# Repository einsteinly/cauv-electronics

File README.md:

**This repository has been moved to https://github.com/CambridgeAUV/cauv_electronics and is no longer maintained**

# cauv-electronics

This is the electronics repository for our newest vehicle. This library is dependent on the Adam Greig KiCAD library. Additional components are added in the cauv_lib directory.

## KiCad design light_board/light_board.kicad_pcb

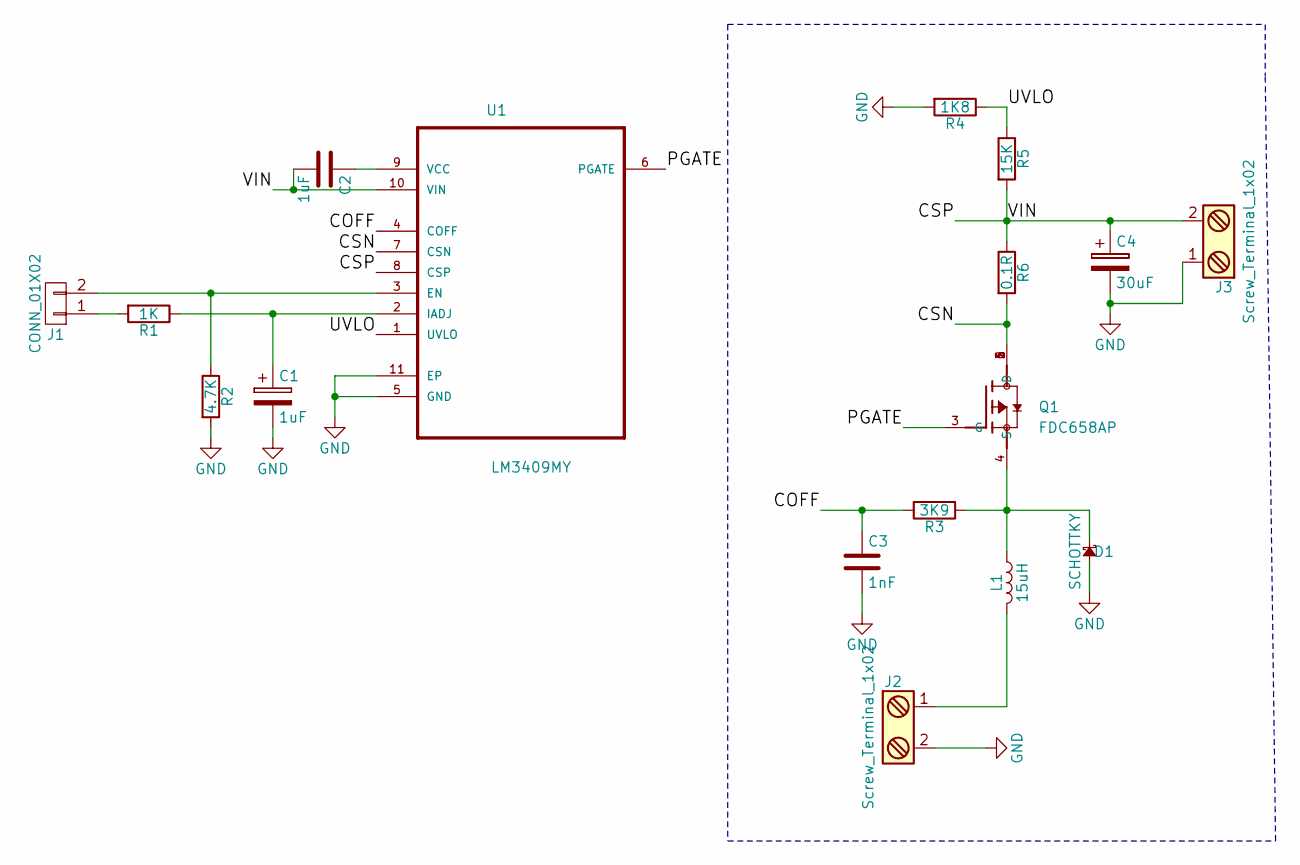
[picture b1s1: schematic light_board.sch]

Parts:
C1: 1uF; CP_Radial_Tantal_D5.0mm_P2.50mm
C2: 1uF; 0805
C3: 1nF; 0805
C4: 30uF; CP_Radial_Tantal_D5.0mm_P2.50mm
D1: SCHOTTKY; D_5KPW_P7.62mm_Vertical_AnodeUp
J1: CONN_01X02; Pin_Header_Straight_1x02_Pitch2.54mm
J2, J3: Screw_Terminal_1x02; POWER_CONN
L1: 15uH; L_Axial_L16.0mm_D6.3mm_P25.40mm_Horizontal_Fastron_VHBCC
Q1: FDC658AP; FDC658AP FDC658AP
R1: 1K; 0805
R2: 4.7K; 0805
R3: 3K9; 0805
R4: 1K8; 0805
R5: 15K; 0805
R6: 0.1R; R_Axial_DIN0614_L14.3mm_D5.7mm_P15.24mm_Horizontal
U1: LM3409MY; LM3409

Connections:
/COFF: C3.1, R3.2, U1.4 (COFF)
/CSN: Q1.1 (D), Q1.2 (D), Q1.5 (D), Q1.6 (D), R6.2, U1.7 (CSN)
/CSP: C2.2, C4.1, J3.2, R5.2, R6.1, U1.8 (CSP), U1.10 (VIN)
/PGATE: Q1.3 (G), U1.6 (PGATE)
/UVLO: R4.1, R5.1, U1.1 (UVLO)
GND: C1.2, C3.2, C4.2, D1.2, J2.2, J3.1, R2.2, R4.2, U1.5 (GND), U1.11 (EP)
unnamed: C1.1, R1.1, U1.2 (IADJ)
unnamed: C2.1, U1.9 (VCC)
unnamed: D1.1, L1.1, Q1.4 (S), R3.1
unnamed: J1.1, R1.2
unnamed: J1.2, R2.1, U1.3 (EN)
unnamed: J2.1, L1.2

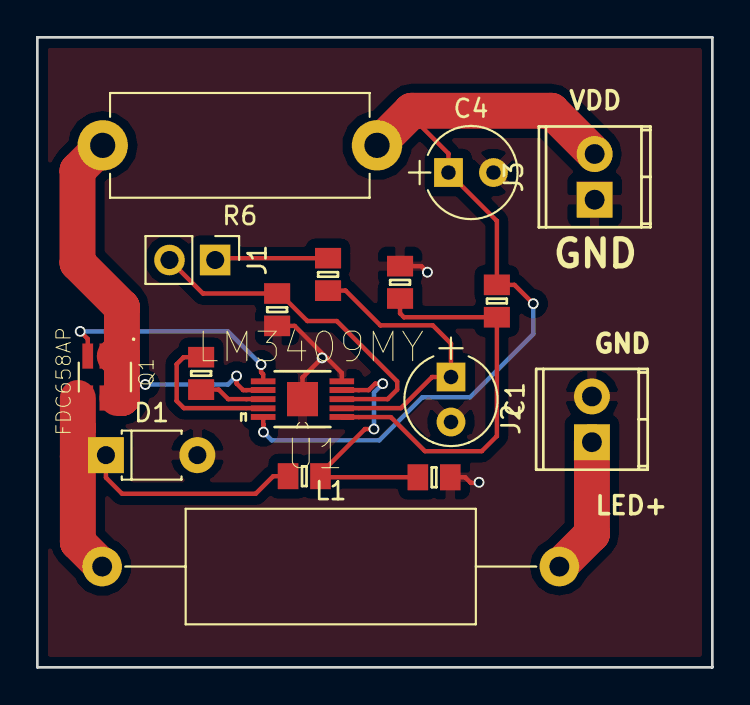
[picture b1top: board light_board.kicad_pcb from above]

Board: 2 copper layers, 37.5 x 35.0 mm, 17 parts (0 on the bottom side), 12 nets.

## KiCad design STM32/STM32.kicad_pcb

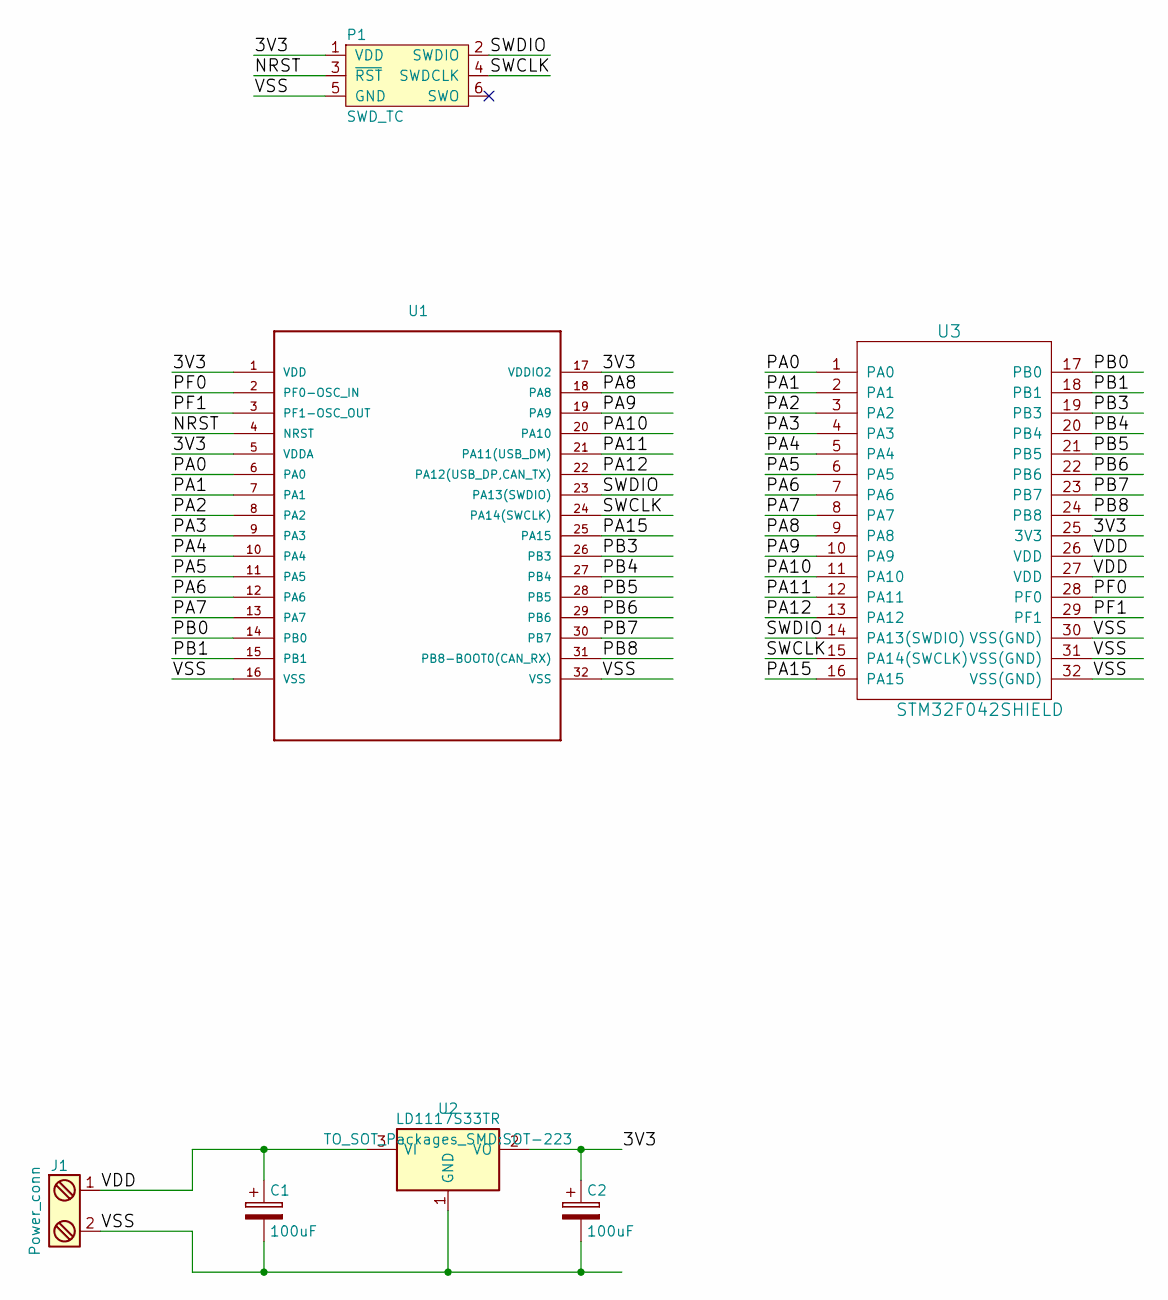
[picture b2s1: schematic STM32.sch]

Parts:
C1, C2: 100uF; CP_Radial_D4.0mm_P1.50mm
J1: Power_conn; TerminalBlock_Pheonix_MPT-2.54mm_2pol
P1: SWD_TC; SWD_CONN
U1: STM32F042K4; LQFP-32
U2: LD1117S33TR; SOT-223
U3: STM32F042SHIELD; STM32F042_SHIELD

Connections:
/3V3: C2.1, P1.1 (VDD), U1.1 (VDD), U1.5 (VDDA), U1.17 (VDDIO2), U2.2 (VO), U3.25 (3V3)
/NRST: P1.3 (~RST), U1.4 (NRST)
/PA0: U1.6 (PA0), U3.1 (PA0)
/PA1: U1.7 (PA1), U3.2 (PA1)
/PA2: U1.8 (PA2), U3.3 (PA2)
/PA3: U1.9 (PA3), U3.4 (PA3)
/PA4: U1.10 (PA4), U3.5 (PA4)
/PA5: U1.11 (PA5), U3.6 (PA5)
/PA6: U1.12 (PA6), U3.7 (PA6)
/PA7: U1.13 (PA7), U3.8 (PA7)
/PA8: U1.18 (PA8), U3.9 (PA8)
/PA9: U1.19 (PA9), U3.10 (PA9)
/PA10: U1.20 (PA10), U3.11 (PA10)
/PA11: U1.21 (PA11(USB_DM)), U3.12 (PA11)
/PA12: U1.22 (PA12(USB_DP,CAN_TX)), U3.13 (PA12)
/PA15: U1.25 (PA15), U3.16 (PA15)
/PB0: U1.14 (PB0), U3.17 (PB0)
/PB1: U1.15 (PB1), U3.18 (PB1)
/PB3: U1.26 (PB3), U3.19 (PB3)
/PB4: U1.27 (PB4), U3.20 (PB4)
/PB5: U1.28 (PB5), U3.21 (PB5)
/PB6: U1.29 (PB6), U3.22 (PB6)
/PB7: U1.30 (PB7), U3.23 (PB7)
/PB8: U1.31 (PB8-BOOT0(CAN_RX)), U3.24 (PB8)
/PF0: U1.2 (PF0-OSC_IN), U3.28 (PF0)
/PF1: U1.3 (PF1-OSC_OUT), U3.29 (PF1)
/SWCLK: P1.4 (SWDCLK), U1.24 (PA14(SWCLK)), U3.15 (PA14(SWCLK))
/SWDIO: P1.2 (SWDIO), U1.23 (PA13(SWDIO)), U3.14 (PA13(SWDIO))
/VDD: C1.1, J1.1, U2.3 (VI), U3.26 (VDD), U3.27 (VDD)
/VSS: C1.2, C2.2, J1.2, P1.5 (GND), U1.16 (VSS), U1.32 (VSS), U2.1 (GND), U3.30 (VSS(GND)), U3.31 (VSS(GND)), U3.32 (VSS(GND))

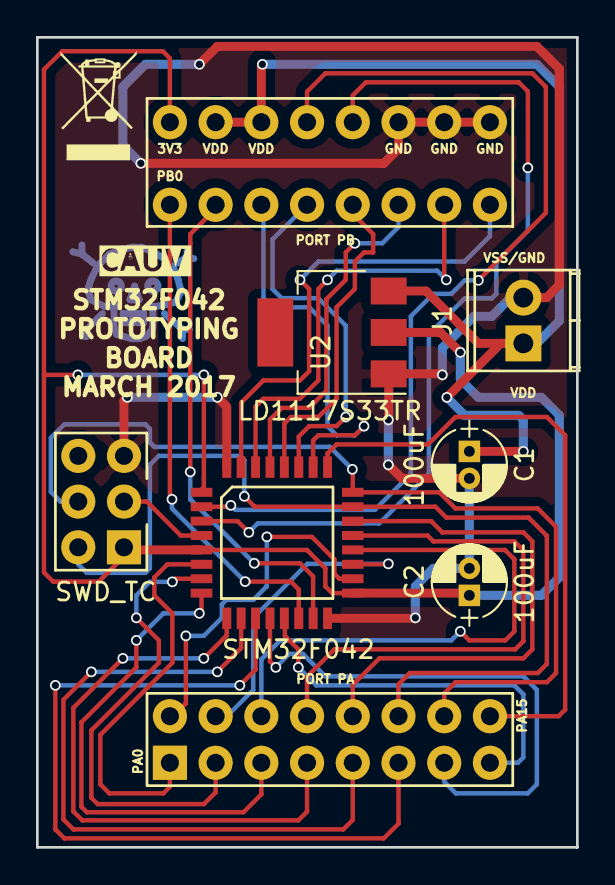
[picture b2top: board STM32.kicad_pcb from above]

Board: 2 copper layers, 30.0 x 45.0 mm, 7 parts (0 on the bottom side), 30 nets.

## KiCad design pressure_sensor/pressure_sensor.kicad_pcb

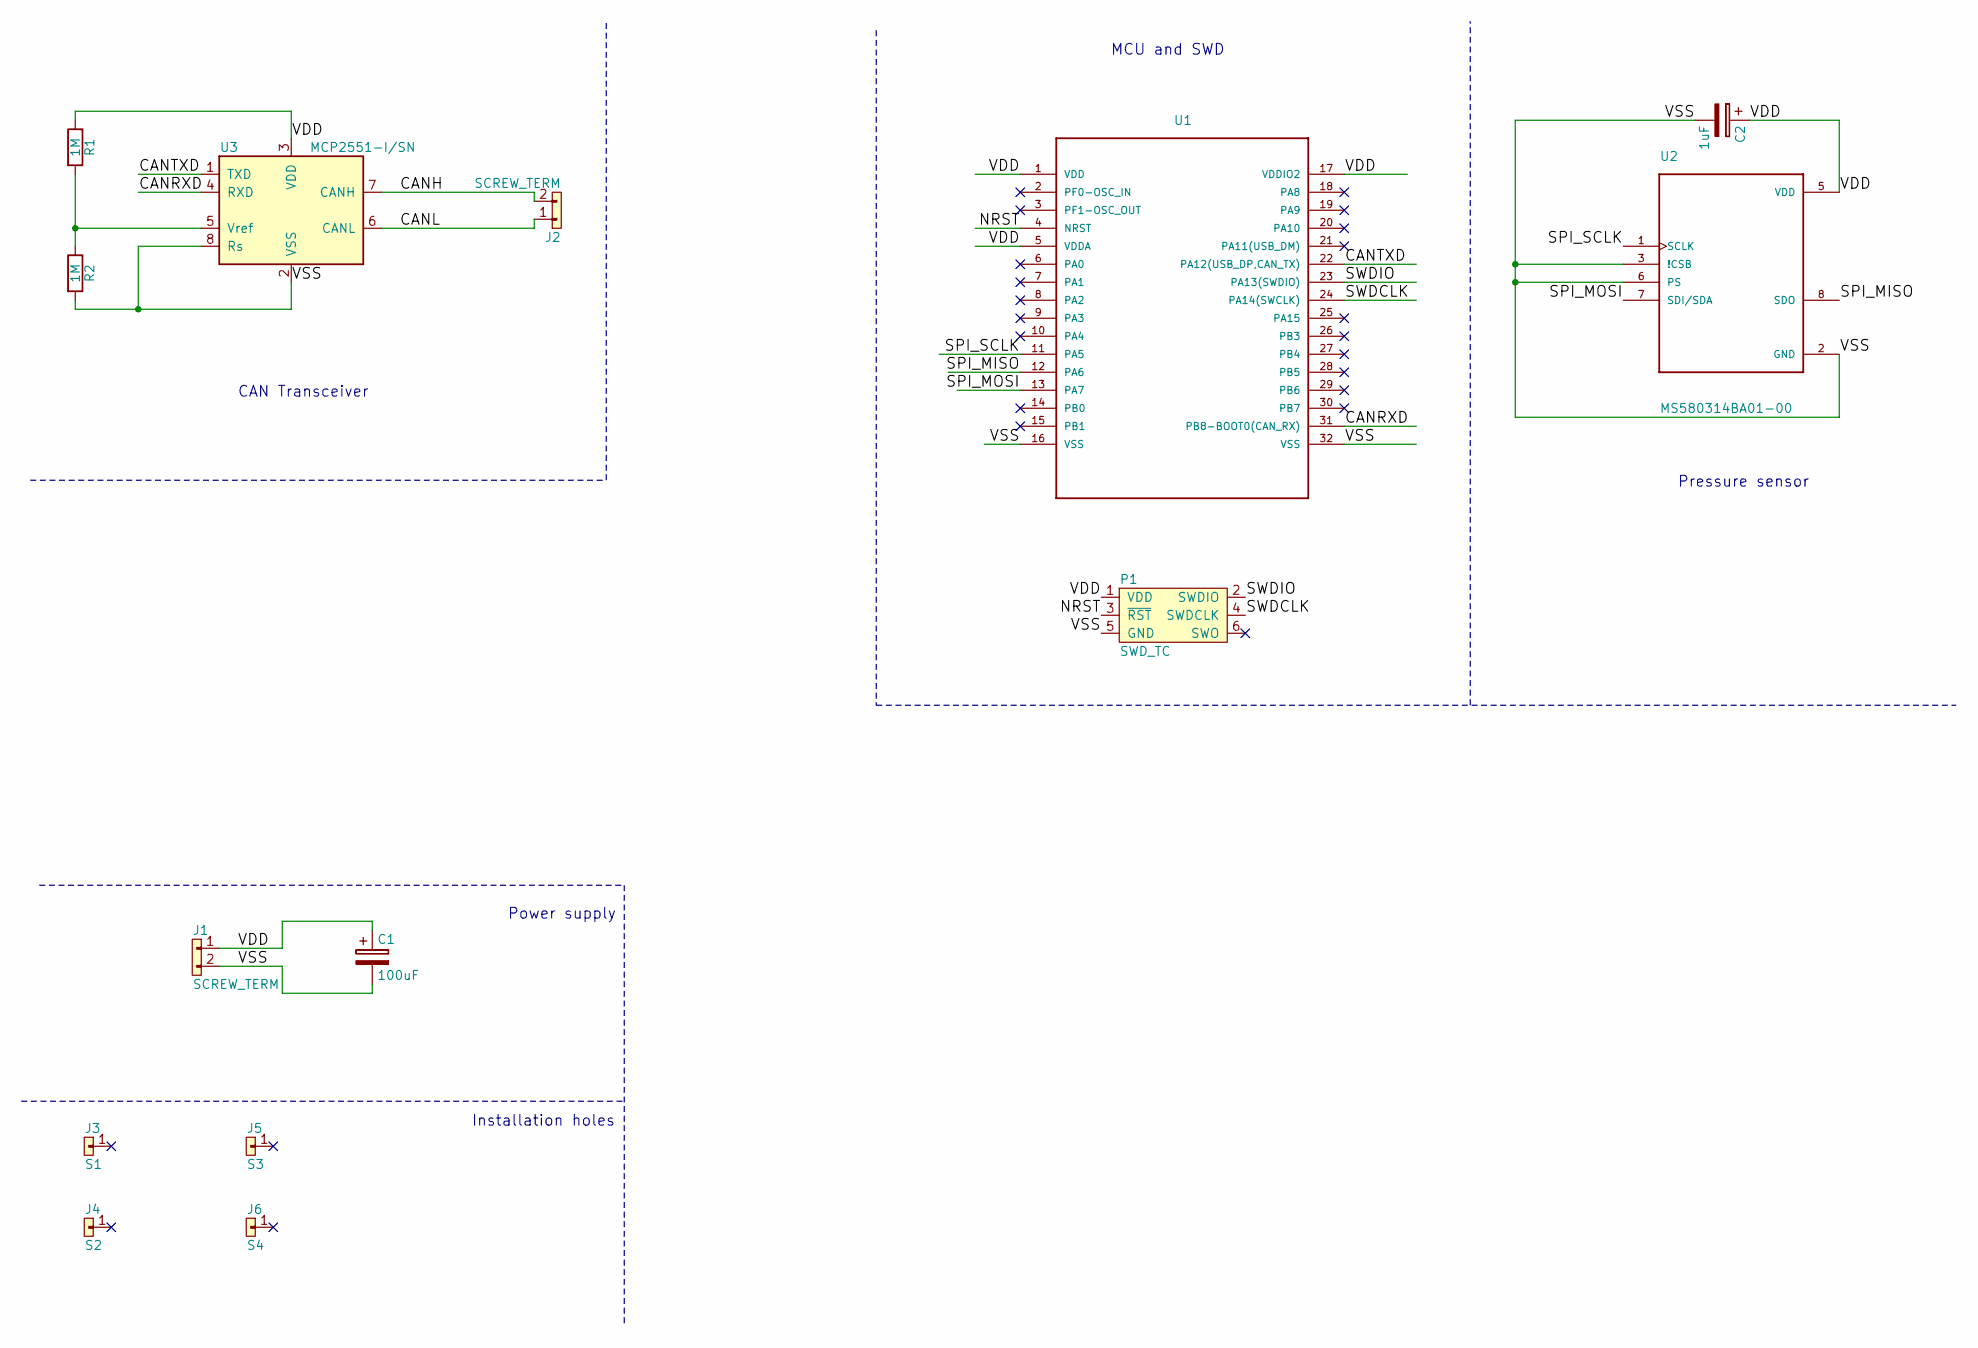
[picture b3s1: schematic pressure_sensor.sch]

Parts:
C1: 100uF; CP_Radial_D4.0mm_P1.50mm
C2: 1uF; CP_Radial_D4.0mm_P1.50mm
J1, J2: SCREW_TERM; TerminalBlock_Pheonix_PT-3.5mm_2pol
J3: S1; SIL-254P-01
J4: S2; SIL-254P-01
J5: S3; SIL-254P-01
J6: S4; SIL-254P-01
P1: SWD_TC; SWD_CONN
R1, R2: 1M; R_Axial_DIN0204_L3.6mm_D1.6mm_P5.08mm_Horizontal
U1: STM32F042K4; LQFP-32
U2: MS580314BA01-00; XDCR_MS580314BA01-00
U3: MCP2551-I/SN; SOIC-8-N

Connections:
/CANH: J2.2, U3.7 (CANH)
/CANL: J2.1, U3.6 (CANL)
/CANRXD: U1.31 (PB8-BOOT0(CAN_RX)), U3.4 (RXD)
/CANTXD: U1.22 (PA12(USB_DP,CAN_TX)), U3.1 (TXD)
/NRST: P1.3 (~RST), U1.4 (NRST)
/SPI_MISO: U1.12 (PA6), U2.8 (SDO)
/SPI_MOSI: U1.13 (PA7), U2.7 (SDI/SDA)
/SPI_SCLK: U1.11 (PA5), U2.1 (SCLK)
/SWDCLK: P1.4 (SWDCLK), U1.24 (PA14(SWCLK))
/SWDIO: P1.2 (SWDIO), U1.23 (PA13(SWDIO))
/VDD: C1.1, C2.1, J1.1, P1.1 (VDD), R1.1, U1.1 (VDD), U1.5 (VDDA), U1.17 (VDDIO2), U2.5 (VDD), U3.3 (VDD)
/VSS: C1.2, C2.2, J1.2, P1.5 (GND), R2.2, U1.16 (VSS), U1.32 (VSS), U2.2 (GND), U2.3 (!CSB), U2.6 (PS), U3.2 (VSS), U3.8 (Rs)
unnamed: R1.2, R2.1, U3.5 (Vref)

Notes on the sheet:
CAN Transceiver
MCU and SWD
Pressure sensor
Power supply
Installation holes

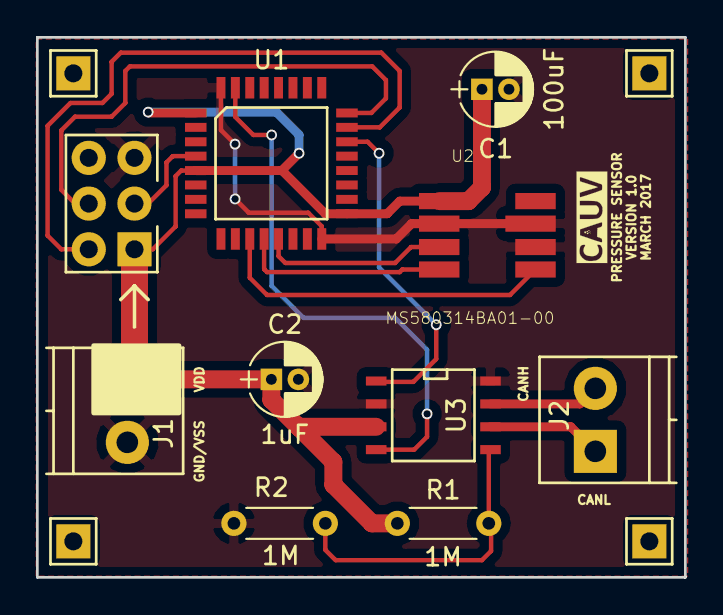
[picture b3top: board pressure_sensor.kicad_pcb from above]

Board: 2 copper layers, 36.0 x 30.0 mm, 14 parts (0 on the bottom side), 13 nets.

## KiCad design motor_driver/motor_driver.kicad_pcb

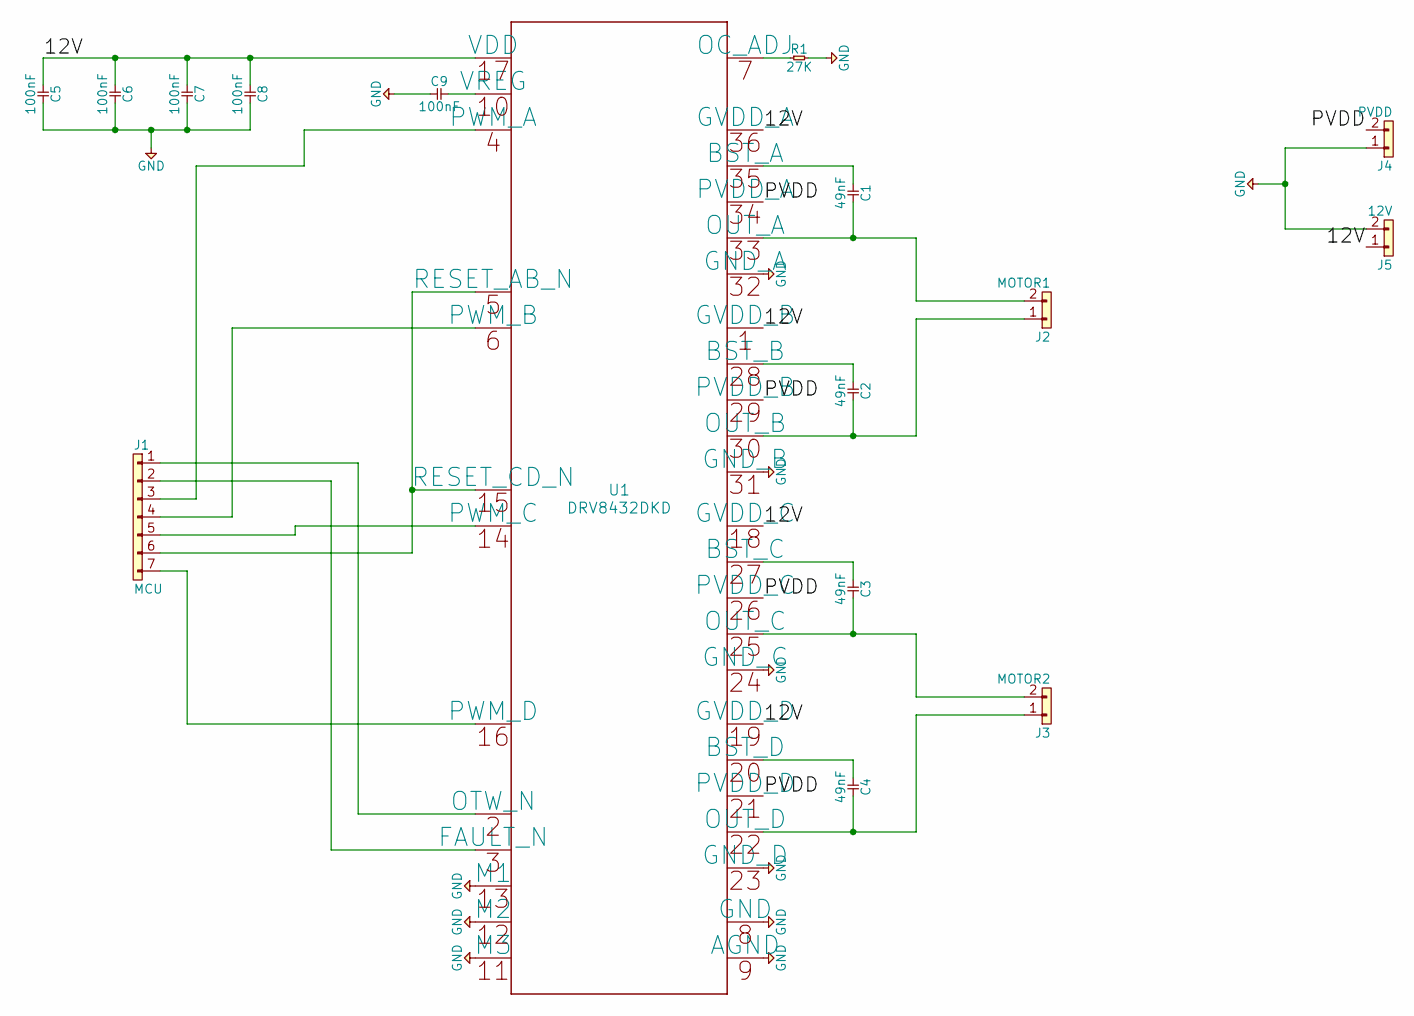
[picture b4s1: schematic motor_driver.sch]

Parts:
C1, C2, C3, C4: 49nF; 0805
C5, C6, C7, C8, C9: 100nF; 0805
J1: MCU; SIL-254P-07
J2: MOTOR1; SIL-254P-02
J3: MOTOR2; SIL-254P-02
J4: PVDD; SIL-254P-02
J5: 12V; SIL-254P-02
R1: 27K; 0805
U1: DRV8432DKD; DRV8432DKDR

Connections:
/12V: C5.1, C6.1, C7.1, C8.1, J5.1, U1.1 (GVDD_B), U1.17 (VDD), U1.18 (GVDD_C), U1.19 (GVDD_D), U1.36 (GVDD_A)
/PVDD: J4.2, U1.21 (PVDD_D), U1.26 (PVDD_C), U1.29 (PVDD_B), U1.34 (PVDD_A)
GND: C5.2, C6.2, C7.2, C8.2, C9.1, J4.1, J5.2, R1.2, U1.8 (GND), U1.9 (AGND), U1.11 (M3), U1.12 (M2), U1.13 (M1), U1.23 (GND_D), U1.24 (GND_C), U1.31 (GND_B), U1.32 (GND_A)
unnamed: C1.1, U1.35 (BST_A)
unnamed: C1.2, J2.2, U1.33 (OUT_A)
unnamed: C2.1, U1.28 (BST_B)
unnamed: C2.2, J2.1, U1.30 (OUT_B)
unnamed: C3.1, U1.27 (BST_C)
unnamed: C3.2, J3.2, U1.25 (OUT_C)
unnamed: C4.1, U1.20 (BST_D)
unnamed: C4.2, J3.1, U1.22 (OUT_D)
unnamed: C9.2, U1.10 (VREG)
unnamed: J1.1, U1.2 (OTW_N)
unnamed: J1.2, U1.3 (FAULT_N)
unnamed: J1.3, U1.4 (PWM_A)
unnamed: J1.4, U1.6 (PWM_B)
unnamed: J1.5, U1.14 (PWM_C)
unnamed: J1.6, U1.5 (RESET_AB_N), U1.15 (RESET_CD_N)
unnamed: J1.7, U1.16 (PWM_D)
unnamed: R1.1, U1.7 (OC_ADJ)

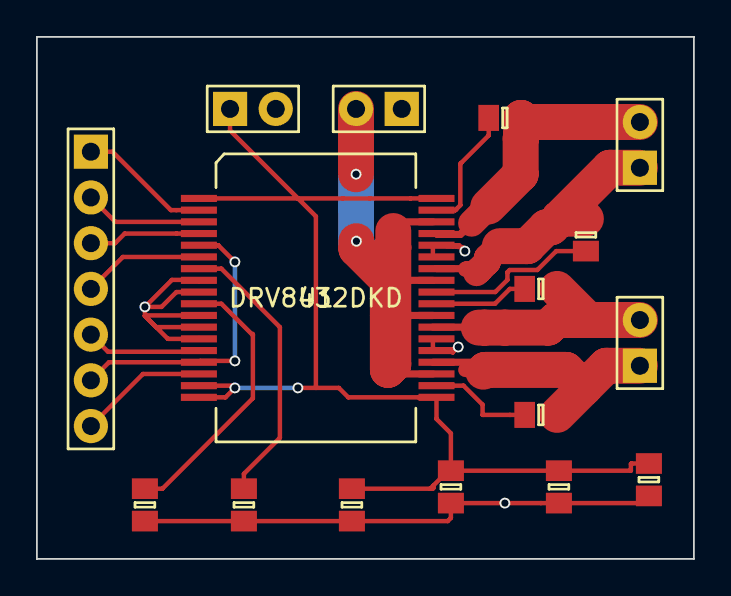
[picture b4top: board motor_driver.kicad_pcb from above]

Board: 2 copper layers, 36.5 x 29.0 mm, 16 parts (0 on the bottom side), 20 nets.

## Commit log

2017-03-23 finished pressure sensor board
2017-03-24 finished pressure sensor
2017-03-24 added motor driver
2017-03-24 added logo to sensor
2017-03-24 made it more beautiful
2017-03-24 added agg library
2017-03-24 added STM shield
2017-03-24 added power conn
2017-03-24 updated power conn
2017-03-24 started lightboard
2017-03-24 finished protoying board
2017-03-24 first version of light board, need to change resistor
2017-06-25 changed design to use large resistor
2017-07-01 checked the light board
2017-07-13 added gerber and drill files
2017-07-15 added dxf for stencils
